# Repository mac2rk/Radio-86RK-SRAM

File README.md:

# Radio-86RK SRAM
The 2012 remake of the 1986 DIY 8-bit computer

## Contents
* [Introduction](#introduction)
* [Specifications](#specifications)
* [Hardware documentation](#hardware-documentation)
  * [Schematic and PCB Layout](#schematic-and-pcb-layout)
  * [Connectors](#connectors)
  * [Bill of Materials](#bill-of-materials)
  * [Memory Map](#memory-map)
* [Firmware documentation](#firmware-documentation)
  * [Monitor](#monitor)
  * [PS/2 adapter](#ps2-adapter)
* [Known Issues](#known-issues)

## Introduction
This project is a 2012 remake of [Radio-86RK](https://en.wikipedia.org/wiki/Radio-86RK), a DIY 8-bit computer the original design for which was published in 1986 by the Soviet *Radio* ham and DIY electronics magazine (hence the "Radio" and "86" in the name).

The original 1986 design targeted an enthusiast building it from scratch and was notable for its relative simplicity. Like most home computers of the era, it uses TV for video output and a cassette tape for program storage. Unlike most home computers, there is no color and no bitmapped graphics. You can get a feel of it via @begoon's excellent online [emulator](https://rk86.ru/) (the emulator's source code is [available on GitHub](https://github.com/begoon/rk86-js)).

The principal motivation behind this project was to replace the obsolete 1-bit DRAM memory and its supporting logic (address multiplexers, etc.) with a single 32KiB static RAM chip. A number of other changes has been made - see the [schematic](Eagle/Radio-86RK-SRAM-Schematic.pdf) for details. The project was initially [published](http://radio86rk.pbworks.com) around 2012 and since then has been built by a number of people, with one build even landing at the [Center for Computing History](http://www.computinghistory.org.uk/det/32376/Radio-86RK-(Russia)/) in Cambridge, thanks to @begoon. Also, this project seems to have inspired other designs, particularly @skiselev's [Radio-86RK](https://github.com/skiselev/radio-86rk) and [Радио-86РК-SRAM-128K](http://www.nedopc.org/forum/viewtopic.php?t=10660&start=0) by @shaos. 

## Specifications
  * CPU: Intel i8080 @ 2MHz
  * Memory: 32KiB RAM, 8 KiB ROM, optional 32KiB ROM cartridge (built-in or external)
  * Display: 64x25 alphanumeric monochrome (50Hz composite video output suitable for TV)
  * Keyboard: Proprietary 66-key (parallel interface) or any standard PS/2 (with built-in adapter)
  * Sound: 1-bit digital
  * I/O: Cassette tape recorder (use [mac2rk](https://github.com/mac2rk/mac2rk) to emulate tape recorder with a sound card)
  * Expansion: optional parallel port (required for ROM cartridges) 
  * Software: 2KiB ROM monitor; additional software can be loaded from a ROM cartridge or tape
  * Form factor: Mini-ITX (170x170 mm, 6.7x6.7 inch)
  * Power supply: 18-36VDC @ approx. 5W via barrel connector

## Hardware documentation

### Schematic and PCB Layout
[Schematic](Eagle/Radio-86RK-SRAM-Schematic.pdf)
[PCB Layout](Eagle/Radio-86RK-SRAM-Silk.pdf)

The computer is built around an Intel i8080 CPU (D6 on the schematic) with i8224 clock generator (D1). RAM and ROM are implemented with 62256 SRAM (D22) and 28C64 EEPROM (D17), respectively. Video subsystem includes an i8275 CRT controller (D8), i8257 DMA controller (D2) with address latch (D7), 28C16 font EEPROM (D12) and a parallel-in, serial-out shift register (D15). Two i8255 Programmable Peripheral Interfaces (PPIs) provide I/O connectivity. One PPI (D20) interfaces a cassete tape recorder and the parallel keyboard; a PS/2 keyboard can be connected via an onboard adapter (D30). The second PPI (D14) implements the expansion port, which can be used, among other things, to connect ROM cartridges. A 28C256 ROM cartridge can be either installed onboard (D30) or connected via a 26-way expansion header. The onboard power supply with power sequencing is built with three DC/DC converter modules (D33..D35) and an opamp (D32).

### Connectors
[Connectors](docs/Connectors.md)

### Bill of Materials
[Bill of Materials](docs/BOM.md)

### Memory Map
[Memory Map](docs/Memory_map.md)

## Firmware Documentation

### Monitor

[Monitor commands and subroutines](docs/Monitor.md)

### PS/2 adapter
The PS/2 to parallel keyboard adapter based on an ATmega48/88/168/328 MCU was developed and [published](https://zx-pk.ru/threads/9294-orion-128-kontroller-ps-2-klaviatury.html) by Kamil Karimov (caro). The source code for the adapter is not available, but the binary is known to work. Note that this adapter requires that the keyboard support Scan Code Set 3. Most do, but some (e.g. Logitech K100) don't and will not work properly with the adapter.

There are two separate versions of the compiled binary: one for ATmega48/88 and one for ATmega168/328. When programming the ATmega, all fuses except CKDIV8 should be left in their default states. CKDIV8 should be left unprogrammed. (CKDIV8 is programmed by default, which clocks the ATmega at 1MHz. With this clock, only Caps Lock (= Rus/Lat) and Print Screen (= Reset) will work normally. Other keys will not work at all or will work partially or intermittently.)

## Known Issues

* Top silkscreen: R109, which sets the current for the "+12V" LED, has a wrong value. Instead oof 330 ohm, it should be between 1kOhm and 1.5kOhm
* PS/2 adapter requires that the keyboard support Scan Code Set 3. Most do, but some (e.g. Logitech K100) don't and do not work properly with the adapter.

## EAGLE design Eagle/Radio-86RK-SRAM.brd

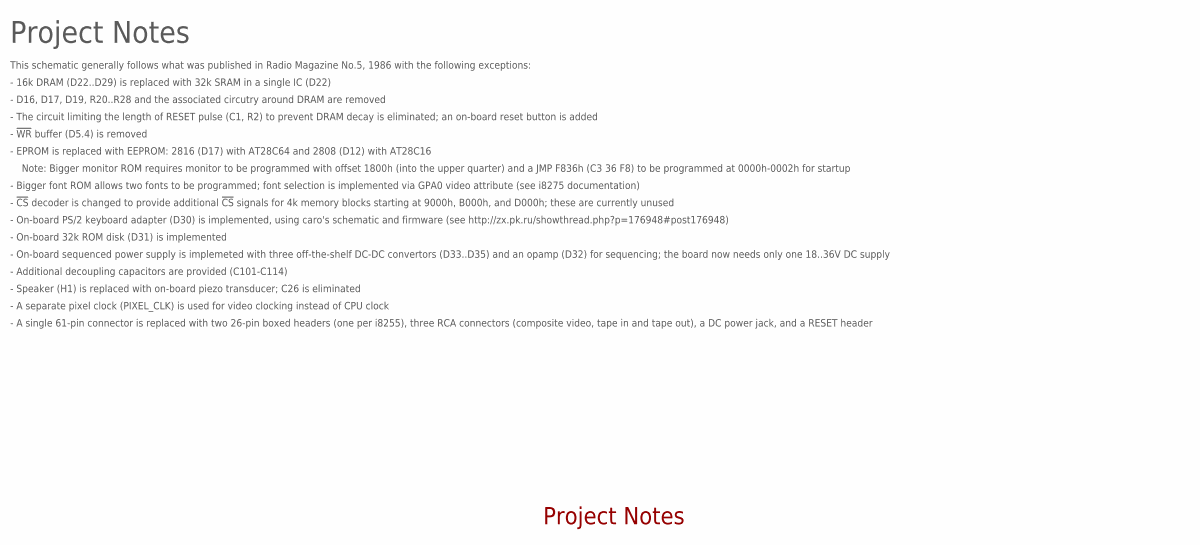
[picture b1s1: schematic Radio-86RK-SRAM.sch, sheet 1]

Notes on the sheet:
Project Notes
This schematic generally follows what was published in Radio Magazine No.5, 1986 with the following exceptions:
- 16k DRAM (D22..D29) is replaced with 32k SRAM in a single IC (D22)
- D16, D17, D19, R20..R28 and the associated circutry around DRAM are removed
- EPROM is replaced with EEPROM: 2816 (D17) with AT28C64 and 2808 (D12) with AT28C16
- !WR! buffer (D5.4) is removed
- !CS! decoder is changed to provide additional !CS! signals for 4k memory blocks starting at 9000h, B000h, and D000h; these are currently unused
Note: Bigger monitor ROM requires monitor to be programmed with offset 1800h (into the upper quarter) and a JMP F836h (C3 36 F8) to be programmed at 0000h-0002h for startup
- Bigger font ROM allows two fonts to be programmed; font selection is implemented via GPA0 video attribute (see i8275 documentation)
- On-board sequenced power supply is implemeted with three off-the-shelf DC-DC convertors (D33..D35) and an opamp (D32) for sequencing; the board now needs only one 18..36V DC supply
- Additional decoupling capacitors are provided (C101-C114)
- On-board PS/2 keyboard adapter (D30) is implemented, using caro's schematic and firmware (see http://zx.pk.ru/showthread.php?p=176948#post176948)
- On-board 32k ROM disk (D31) is implemented
- Speaker (H1) is replaced with on-board piezo transducer; C26 is eliminated
- A separate pixel clock (PIXEL_CLK) is used for video clocking instead of CPU clock
- A single 61-pin connector is replaced with two 26-pin boxed headers (one per i8255), three RCA connectors (composite video, tape in and tape out), a DC power jack, and a RESET header
- The circuit limiting the length of RESET pulse (C1, R2) to prevent DRAM decay is eliminated; an on-board reset button is added

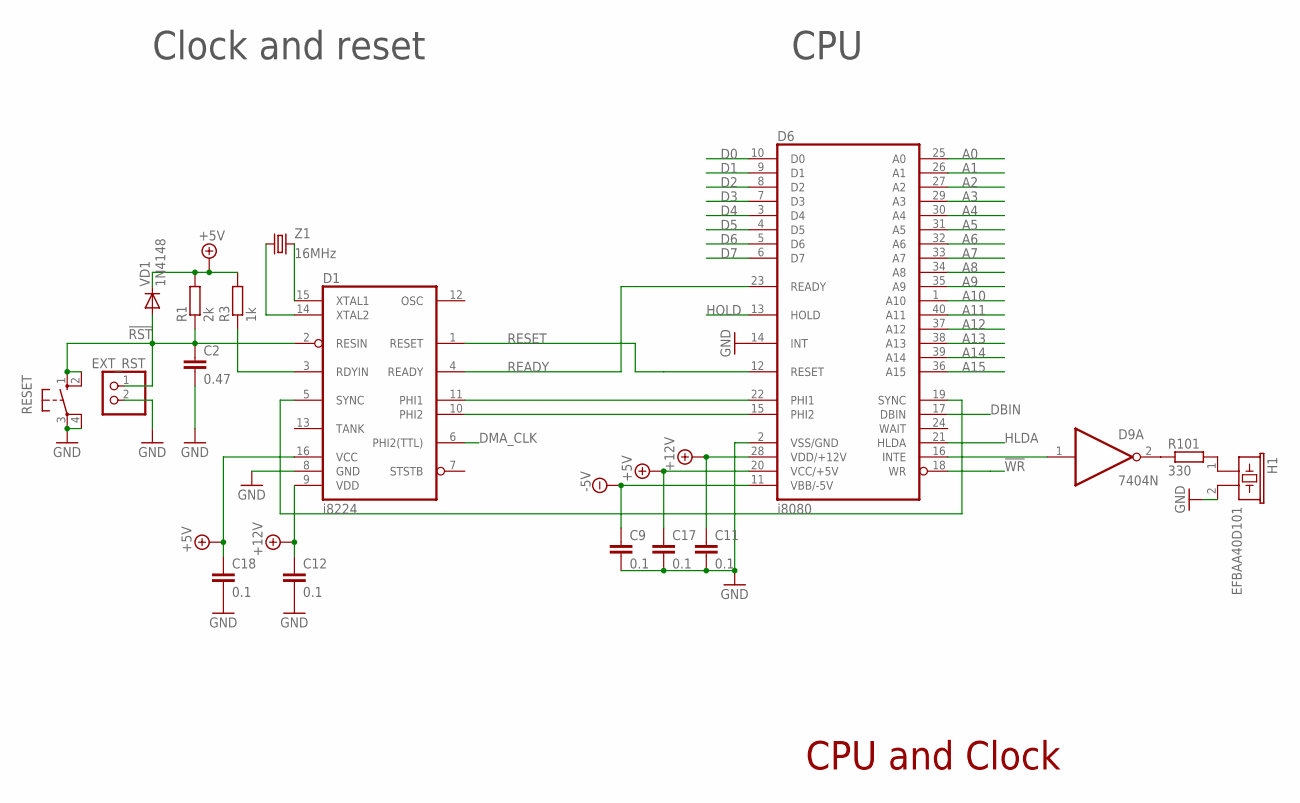
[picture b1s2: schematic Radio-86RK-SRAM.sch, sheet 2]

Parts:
C2: 0.47; C050-024X044
C9, C11, C12, C17, C18: 0.1; C050-024X044
D1: i8224; DIL16
D6: i8080; DIL40
D9: 7404N; DIL14
EXT_RST: PINHD-1X2; 1X02
H1: EFBAA40D101
R1: 2k; 0207/10
R3: 1k; 0207/10
R101: 330; 0207/10
RESET: 10-XX; B3F-10XX
VD1: 1N4148; DO35-10
Z1: 16MHz; HC49U-V

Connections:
!RST: C2.1, D1.2 (RESIN), EXT_RST.1, R1.1, RESET.1 (S), RESET.2 (S1), VD1.A; also elsewhere on the board
!WR: D6.18 (WR); also elsewhere on the board
+5V: C17.1, C18.1, D1.16 (VCC), D6.20 (VCC/+5V), R1.2, R3.2, VD1.C; also elsewhere on the board
+12V: C11.1, C12.1, D1.9 (VDD), D6.28 (VDD/+12V); also elsewhere on the board
-5V: C9.1, D6.11 (VBB/-5V); also elsewhere on the board
A0: D6.25 (A0); also elsewhere on the board
A1: D6.26 (A1); also elsewhere on the board
A2: D6.27 (A2); also elsewhere on the board
A3: D6.29 (A3); also elsewhere on the board
A4: D6.30 (A4); also elsewhere on the board
A5: D6.31 (A5); also elsewhere on the board
A6: D6.32 (A6); also elsewhere on the board
A7: D6.33 (A7); also elsewhere on the board
A8: D6.34 (A8); also elsewhere on the board
A9: D6.35 (A9); also elsewhere on the board
A10: D6.1 (A10); also elsewhere on the board
A11: D6.40 (A11); also elsewhere on the board
A12: D6.37 (A12); also elsewhere on the board
A13: D6.38 (A13); also elsewhere on the board
A14: D6.39 (A14); also elsewhere on the board
A15: D6.36 (A15); also elsewhere on the board
D0: D6.10 (D0); also elsewhere on the board
D1: D6.9 (D1); also elsewhere on the board
D2: D6.8 (D2); also elsewhere on the board
D3: D6.7 (D3); also elsewhere on the board
D4: D6.3 (D4); also elsewhere on the board
D5: D6.4 (D5); also elsewhere on the board
D6: D6.5 (D6); also elsewhere on the board
D7: D6.6 (D7); also elsewhere on the board
DBIN: D6.17 (DBIN); also elsewhere on the board
DMA_CLK: D1.6 (PHI2(TTL)); also elsewhere on the board
GND: C2.2, C9.2, C11.2, C12.2, C17.2, C18.2, D1.8 (GND), D6.2 (VSS/GND), D6.14 (INT), EXT_RST.2, H1.2, RESET.3, RESET.4 (P1); also elsewhere on the board
HLDA: D6.21 (HLDA); also elsewhere on the board
HOLD: D6.13 (HOLD); also elsewhere on the board
unnamed: D1.11 (PHI1), D6.22 (PHI1)
unnamed: D1.10 (PHI2), D6.15 (PHI2)
unnamed: D1.15 (XTAL1), Z1.2
unnamed: D1.14 (XTAL2), Z1.1
unnamed: D1.5 (SYNC), D6.19 (SYNC)
unnamed: D1.3 (RDYIN), R3.1
unnamed: D6.16 (INTE), D9.1 (I)
unnamed: H1.1, R101.2
unnamed: D9.2 (O), R101.1
READY: D1.4 (READY), D6.23 (READY); also elsewhere on the board
RESET: D1.1 (RESET), D6.12 (RESET); also elsewhere on the board

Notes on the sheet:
CPU and Clock
Clock and reset
CPU

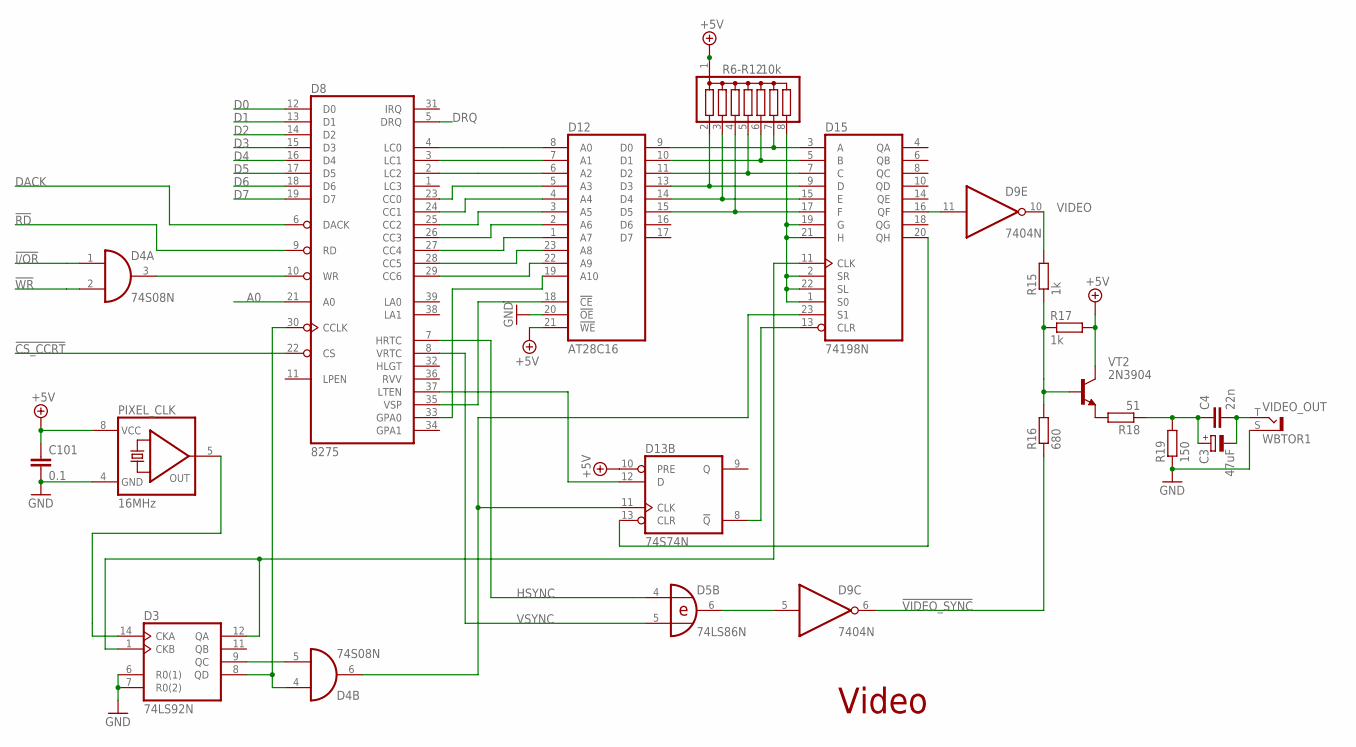
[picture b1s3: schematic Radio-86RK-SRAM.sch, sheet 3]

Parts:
C3: 47uF; E2,5-5
C4: 22n; C050-024X044
C101: 0.1; C050-024X044
D3: 74LS92N; DIL14
D4: 74S08N; DIL14
D5: 74LS86N; DIL14
D8: 8275; DIL40
D9: 7404N; DIL14
D12: AT28C16; DIL24
D13: 74S74N; DIL14
D15: 74198N; DIL24-6
PIXEL_CLK: 16MHz; DIL08S
R6-R12: 10k; SIL8
R15, R17: 1k; 0207/10
R16: 680; 0207/10
R18: 51; 0207/10
R19: 150; 0207/10
VIDEO_OUT: WBTOR1; MPN WBTOR 1 BLACK
VT2: 2N3904; TO92

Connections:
!CS_CCRT: D8.22 (CS); also elsewhere on the board
!I/OR: D4.1 (I0); also elsewhere on the board
!RD: D8.9 (RD); also elsewhere on the board
!VIDEO: D9.11 (I), D15.16 (QF)
!VIDEO_SYNC: D9.6 (O), R16.1
!WR: D4.2 (I1); also elsewhere on the board
+5V: C101.1, D12.21 (!WE), D13.10 (PRE), PIXEL_CLK.8 (VCC), R6-R12.1, R17.2, VT2.1 (C); also elsewhere on the board
A0: D8.21 (A0); also elsewhere on the board
COMPOSITE_VIDEO: C3.-, C4.2, VIDEO_OUT.T
D0: D8.12 (D0); also elsewhere on the board
D1: D8.13 (D1); also elsewhere on the board
D2: D8.14 (D2); also elsewhere on the board
D3: D8.15 (D3); also elsewhere on the board
D4: D8.16 (D4); also elsewhere on the board
D5: D8.17 (D5); also elsewhere on the board
D6: D8.18 (D6); also elsewhere on the board
D7: D8.19 (D7); also elsewhere on the board
DACK: D8.6 (DACK); also elsewhere on the board
DRQ: D8.5 (DRQ); also elsewhere on the board
GND: C101.2, D3.6 (R0(1)), D3.7 (R0(2)), D12.20 (!OE), PIXEL_CLK.4 (GND), R19.1, VIDEO_OUT.S; also elsewhere on the board
HSYNC: D5.4 (I0), D8.7 (HRTC)
unnamed: D3.14 (CKA), PIXEL_CLK.5 (OUT)
unnamed: D3.1 (CKB), D3.12 (QA), D15.11 (CLK)
unnamed: D4.3 (O), D8.10 (WR)
unnamed: D3.9 (QC), D4.5 (I1)
unnamed: D3.8 (QD), D4.4 (I0), D8.30 (CCLK)
unnamed: D8.23 (CC0), D12.5 (A3)
unnamed: D8.24 (CC1), D12.4 (A4)
unnamed: D8.25 (CC2), D12.3 (A5)
unnamed: D8.26 (CC3), D12.2 (A6)
unnamed: D8.27 (CC4), D12.1 (A7)
unnamed: D8.4 (LC0), D12.8 (A0)
unnamed: D8.3 (LC1), D12.7 (A1)
unnamed: D8.2 (LC2), D12.6 (A2)
unnamed: D8.35 (VSP), D12.18 (!CE)
unnamed: D12.9 (D0), D15.3 (A), R6-R12.7
unnamed: D8.28 (CC5), D12.23 (A8)
unnamed: D8.29 (CC6), D12.22 (A9)
unnamed: D12.10 (D1), D15.5 (B), R6-R12.6
unnamed: D12.11 (D2), D15.7 (C), R6-R12.5
unnamed: D12.13 (D3), D15.9 (D), R6-R12.2
unnamed: D12.14 (D4), D15.15 (E), R6-R12.3
unnamed: D12.15 (D5), D15.17 (F), R6-R12.4
unnamed: D13.13 (CLR), D15.20 (QH)
unnamed: D13.8 (!Q), D15.13 (CLR)
unnamed: D4.6 (O), D13.11 (CLK), D15.23 (S1)
unnamed: D8.37 (LTEN), D13.12 (D)
unnamed: R15.1, R16.2, R17.1, VT2.2 (B)
unnamed: D5.6 (O), D9.5 (I)
unnamed: R18.2, VT2.3 (E)
unnamed: C3.+, C4.1, R18.1, R19.2
unnamed: D8.33 (GPA0), D12.19 (A10)
unnamed: D15.1 (S0), D15.2 (SR), D15.19 (G), D15.21 (H), D15.22 (SL), R6-R12.8
VIDEO: D9.10 (O), R15.2
VSYNC: D5.5 (I1), D8.8 (VRTC)

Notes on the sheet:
Video

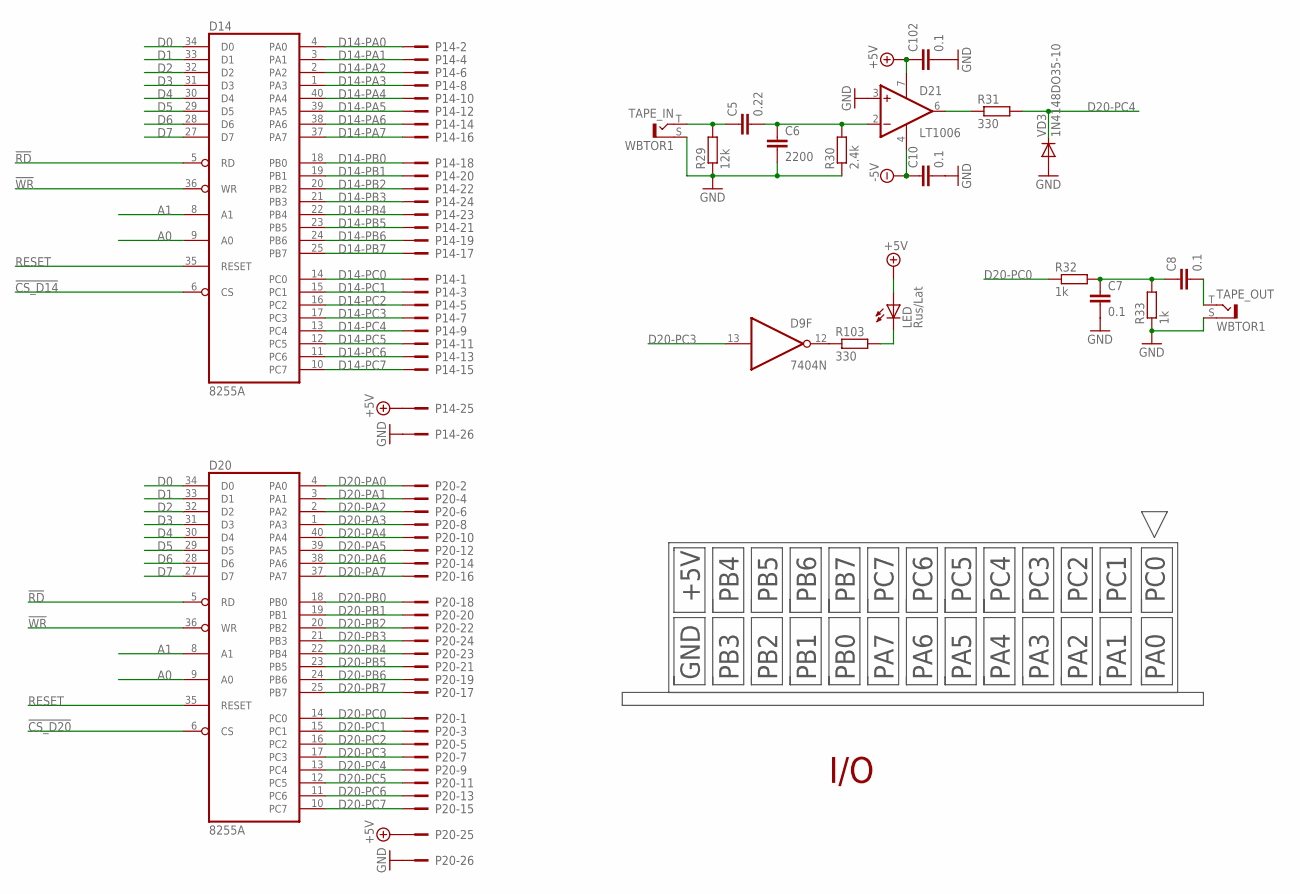
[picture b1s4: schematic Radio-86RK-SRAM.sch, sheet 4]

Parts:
C5: 0.22; C050-024X044
C6: 2200; C050-024X044
C7, C8, C10, C102: 0.1; C050-024X044
D9: 7404N; DIL14
D14, D20: 8255A; DIL40
D21: LT1006; DIL08
LED: Rus/Lat; LED3MM
P14, P20: 2526-5; PAK100/2500-5-26
R29: 12k; 0207/10
R30: 2.4k; 0207/10
R31, R103: 330; 0207/10
R32, R33: 1k; 0207/10
TAPE_IN: WBTOR1; MPN WBTOR 1 BLACK
TAPE_OUT: WBTOR1; MPN WBTOR 1 BLACK
VD3: 1N4148DO35-10; DO35-10

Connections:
!CS_D14: D14.6 (CS); also elsewhere on the board
!CS_D20: D20.6 (CS); also elsewhere on the board
!RD: D14.5 (RD), D20.5 (RD); also elsewhere on the board
!WR: D14.36 (WR), D20.36 (WR); also elsewhere on the board
+5V: C102.1, D21.7 (V+), LED.A, P14.25, P20.25; also elsewhere on the board
-5V: C10.1, D21.4 (V-); also elsewhere on the board
A0: D14.9 (A0), D20.9 (A0); also elsewhere on the board
A1: D14.8 (A1), D20.8 (A1); also elsewhere on the board
D0: D14.34 (D0), D20.34 (D0); also elsewhere on the board
D1: D14.33 (D1), D20.33 (D1); also elsewhere on the board
D2: D14.32 (D2), D20.32 (D2); also elsewhere on the board
D3: D14.31 (D3), D20.31 (D3); also elsewhere on the board
D4: D14.30 (D4), D20.30 (D4); also elsewhere on the board
D5: D14.29 (D5), D20.29 (D5); also elsewhere on the board
D6: D14.28 (D6), D20.28 (D6); also elsewhere on the board
D7: D14.27 (D7), D20.27 (D7); also elsewhere on the board
D14-PA0: D14.4 (PA0), P14.2; also elsewhere on the board
D14-PA1: D14.3 (PA1), P14.4; also elsewhere on the board
D14-PA2: D14.2 (PA2), P14.6; also elsewhere on the board
D14-PA3: D14.1 (PA3), P14.8; also elsewhere on the board
D14-PA4: D14.40 (PA4), P14.10; also elsewhere on the board
D14-PA5: D14.39 (PA5), P14.12; also elsewhere on the board
D14-PA6: D14.38 (PA6), P14.14; also elsewhere on the board
D14-PA7: D14.37 (PA7), P14.16; also elsewhere on the board
D14-PB0: D14.18 (PB0), P14.18; also elsewhere on the board
D14-PB1: D14.19 (PB1), P14.20; also elsewhere on the board
D14-PB2: D14.20 (PB2), P14.22; also elsewhere on the board
D14-PB3: D14.21 (PB3), P14.24; also elsewhere on the board
D14-PB4: D14.22 (PB4), P14.23; also elsewhere on the board
D14-PB5: D14.23 (PB5), P14.21; also elsewhere on the board
D14-PB6: D14.24 (PB6), P14.19; also elsewhere on the board
D14-PB7: D14.25 (PB7), P14.17; also elsewhere on the board
D14-PC0: D14.14 (PC0), P14.1; also elsewhere on the board
D14-PC1: D14.15 (PC1), P14.3; also elsewhere on the board
D14-PC2: D14.16 (PC2), P14.5; also elsewhere on the board
D14-PC3: D14.17 (PC3), P14.7; also elsewhere on the board
D14-PC4: D14.13 (PC4), P14.9; also elsewhere on the board
D14-PC5: D14.12 (PC5), P14.11; also elsewhere on the board
D14-PC6: D14.11 (PC6), P14.13; also elsewhere on the board
D14-PC7: D14.10 (PC7), P14.15; also elsewhere on the board
D20-PA0: D20.4 (PA0), P20.2; also elsewhere on the board
D20-PA1: D20.3 (PA1), P20.4; also elsewhere on the board
D20-PA2: D20.2 (PA2), P20.6; also elsewhere on the board
D20-PA3: D20.1 (PA3), P20.8; also elsewhere on the board
D20-PA4: D20.40 (PA4), P20.10; also elsewhere on the board
D20-PA5: D20.39 (PA5), P20.12; also elsewhere on the board
D20-PA6: D20.38 (PA6), P20.14; also elsewhere on the board
D20-PA7: D20.37 (PA7), P20.16; also elsewhere on the board
D20-PB0: D20.18 (PB0), P20.18; also elsewhere on the board
D20-PB1: D20.19 (PB1), P20.20; also elsewhere on the board
D20-PB2: D20.20 (PB2), P20.22; also elsewhere on the board
D20-PB3: D20.21 (PB3), P20.24; also elsewhere on the board
D20-PB4: D20.22 (PB4), P20.23; also elsewhere on the board
D20-PB5: D20.23 (PB5), P20.21; also elsewhere on the board
D20-PB6: D20.24 (PB6), P20.19; also elsewhere on the board
D20-PB7: D20.25 (PB7), P20.17; also elsewhere on the board
D20-PC0: D20.14 (PC0), P20.1, R32.1
D20-PC1: D20.15 (PC1), P20.3
D20-PC2: D20.16 (PC2), P20.5
D20-PC3: D9.13 (I), D20.17 (PC3), P20.7
D20-PC4: D20.13 (PC4), P20.9, R31.2, VD3.C
D20-PC5: D20.12 (PC5), P20.11; also elsewhere on the board
D20-PC6: D20.11 (PC6), P20.13; also elsewhere on the board
D20-PC7: D20.10 (PC7), P20.15; also elsewhere on the board
GND: C6.2, C7.2, C10.2, C102.2, D21.3 (+IN), P14.26, P20.26, R29.1, R30.1, R33.1, TAPE_IN.S, TAPE_OUT.S, VD3.A; also elsewhere on the board
unnamed: D9.12 (O), R103.1
unnamed: LED.K (C), R103.2
unnamed: C5.2, C6.1, D21.2 (-IN), R30.2
unnamed: C7.1, C8.1, R32.2, R33.2
unnamed: D21.6 (OUT), R31.1
unnamed: C5.1, R29.2, TAPE_IN.T
unnamed: C8.2, TAPE_OUT.T
RESET: D14.35 (RESET), D20.35 (RESET); also elsewhere on the board

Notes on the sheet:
I/O
GND
PB3
PB2
PB1
PB0
PA7
PA6
PA5
PA4
PA3
PA2
PA1
PA0
+5V
PB4
PB5
PB6
PB7
PC7
PC6
PC5
PC4
PC3
PC2
PC1
PC0

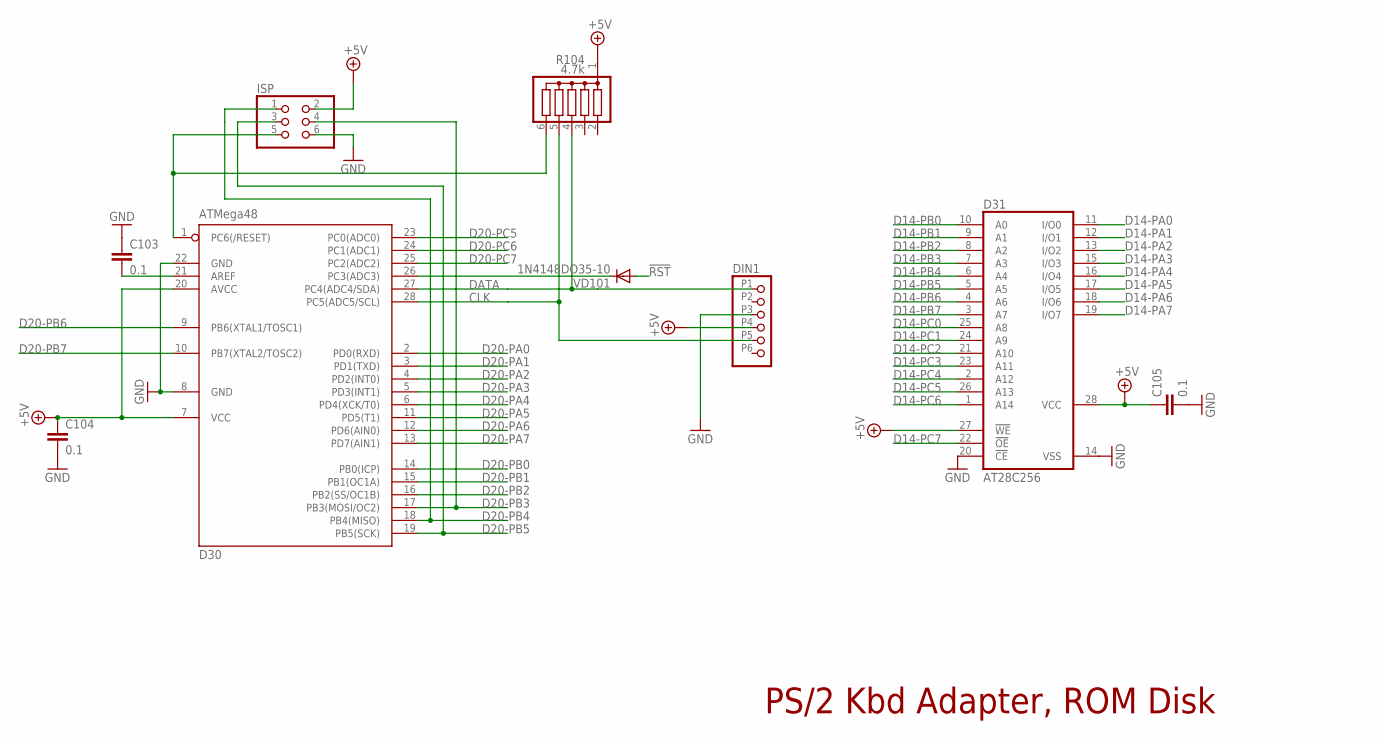
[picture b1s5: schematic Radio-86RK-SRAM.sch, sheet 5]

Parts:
C103, C104, C105: 0.1; C050-024X044
D30: ATMega48; DIL28-3
D31: AT28C256; DIL28-6
DIN1: TM0508A/6; MINI-DIN6
ISP: PINHD-2X3; 2X03
R104: 4.7k; SIL6
VD101: 1N4148DO35-10; DO35-10

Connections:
!RST: VD101.A; also elsewhere on the board
+5V: C104.1, C105.1, D30.7 (VCC), D30.20 (AVCC), D31.27 (!WE), D31.28 (VCC), DIN1.P4 (4), ISP.2, R104.1; also elsewhere on the board
CLK: D30.28 (PC5(ADC5/SCL)), DIN1.P5 (5), R104.5
D14-PA0: D31.11 (I/O0); also elsewhere on the board
D14-PA1: D31.12 (I/O1); also elsewhere on the board
D14-PA2: D31.13 (I/O2); also elsewhere on the board
D14-PA3: D31.15 (I/O3); also elsewhere on the board
D14-PA4: D31.16 (I/O4); also elsewhere on the board
D14-PA5: D31.17 (I/O5); also elsewhere on the board
D14-PA6: D31.18 (I/O6); also elsewhere on the board
D14-PA7: D31.19 (I/O7); also elsewhere on the board
D14-PB0: D31.10 (A0); also elsewhere on the board
D14-PB1: D31.9 (A1); also elsewhere on the board
D14-PB2: D31.8 (A2); also elsewhere on the board
D14-PB3: D31.7 (A3); also elsewhere on the board
D14-PB4: D31.6 (A4); also elsewhere on the board
D14-PB5: D31.5 (A5); also elsewhere on the board
D14-PB6: D31.4 (A6); also elsewhere on the board
D14-PB7: D31.3 (A7); also elsewhere on the board
D14-PC0: D31.25 (A8); also elsewhere on the board
D14-PC1: D31.24 (A9); also elsewhere on the board
D14-PC2: D31.21 (A10); also elsewhere on the board
D14-PC3: D31.23 (A11); also elsewhere on the board
D14-PC4: D31.2 (A12); also elsewhere on the board
D14-PC5: D31.26 (A13); also elsewhere on the board
D14-PC6: D31.1 (A14); also elsewhere on the board
D14-PC7: D31.22 (!OE); also elsewhere on the board
D20-PA0: D30.2 (PD0(RXD)); also elsewhere on the board
D20-PA1: D30.3 (PD1(TXD)); also elsewhere on the board
D20-PA2: D30.4 (PD2(INT0)); also elsewhere on the board
D20-PA3: D30.5 (PD3(INT1)); also elsewhere on the board
D20-PA4: D30.6 (PD4(XCK/T0)); also elsewhere on the board
D20-PA5: D30.11 (PD5(T1)); also elsewhere on the board
D20-PA6: D30.12 (PD6(AIN0)); also elsewhere on the board
D20-PA7: D30.13 (PD7(AIN1)); also elsewhere on the board
D20-PB0: D30.14 (PB0(ICP)); also elsewhere on the board
D20-PB1: D30.15 (PB1(OC1A)); also elsewhere on the board
D20-PB2: D30.16 (PB2(SS/OC1B)); also elsewhere on the board
D20-PB3: D30.17 (PB3(MOSI/OC2)), ISP.4; also elsewhere on the board
D20-PB4: D30.18 (PB4(MISO)), ISP.1; also elsewhere on the board
D20-PB5: D30.19 (PB5(SCK)), ISP.3; also elsewhere on the board
D20-PB6: D30.9 (PB6(XTAL1/TOSC1)); also elsewhere on the board
D20-PB7: D30.10 (PB7(XTAL2/TOSC2)); also elsewhere on the board
D20-PC5: D30.23 (PC0(ADC0)); also elsewhere on the board
D20-PC6: D30.24 (PC1(ADC1)); also elsewhere on the board
D20-PC7: D30.25 (PC2(ADC2)); also elsewhere on the board
DATA: D30.27 (PC4(ADC4/SDA)), DIN1.P1 (1), R104.4
GND: C103.1, C104.2, C105.2, D30.8 (GND), D30.22 (GND), D31.14 (VSS), D31.20 (!CE), DIN1.G1 (GND), DIN1.G2 (GND), DIN1.G3 (GND), DIN1.P3 (3), ISP.6; also elsewhere on the board
unnamed: C103.2, D30.21 (AREF)
unnamed: D30.1 (PC6(/RESET)), ISP.5, R104.6
unnamed: D30.26 (PC3(ADC3)), VD101.C

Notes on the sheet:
PS/2 Kbd Adapter, ROM Disk

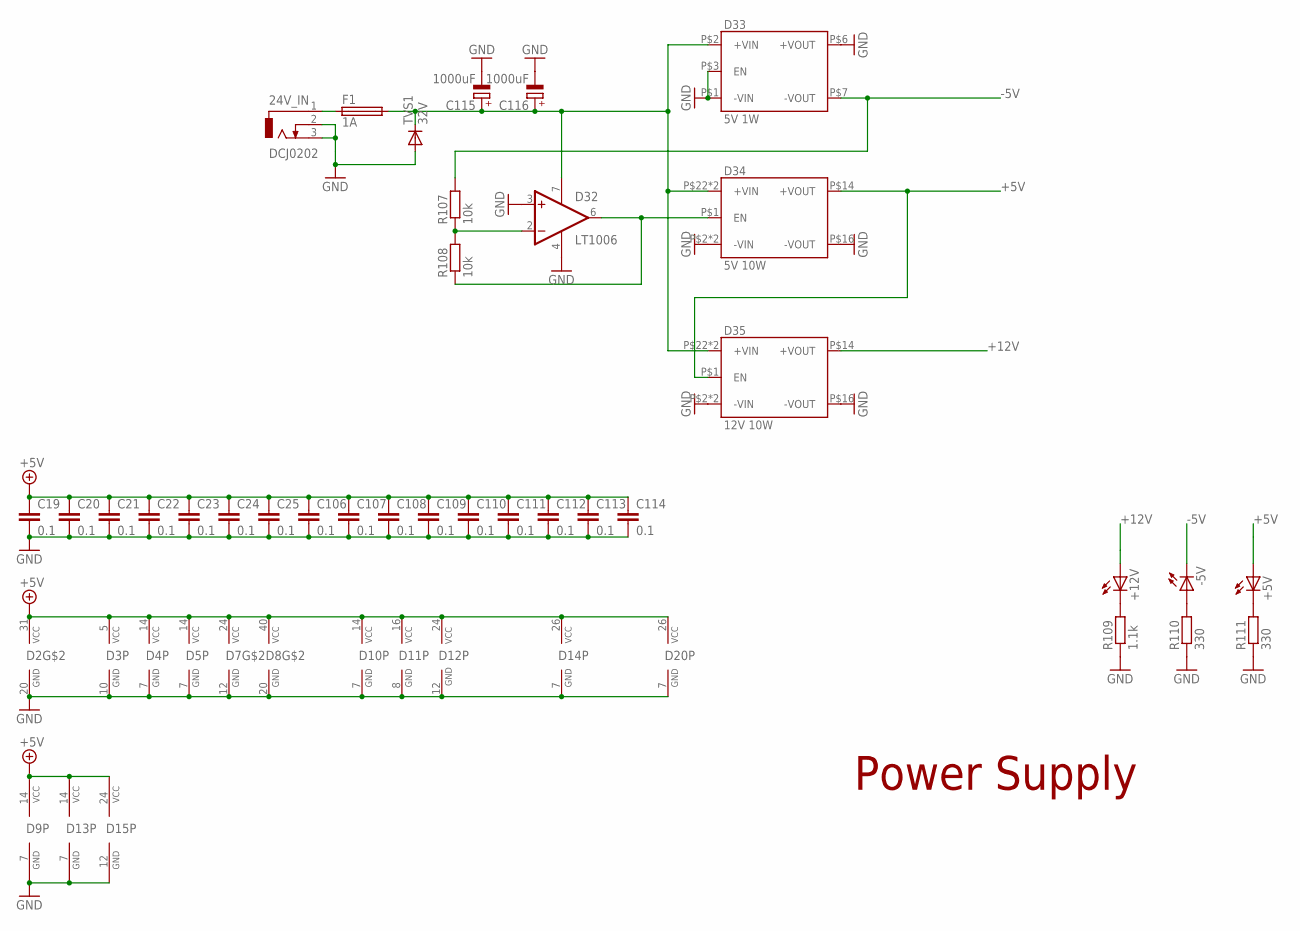
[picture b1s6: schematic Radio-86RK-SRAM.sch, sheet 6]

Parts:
24V_IN: DCJ0202
+5V, +12V: LED3MM
-5V: LED3MM
C19, C20, C21, C22, C23, C24, C25, C106, C107, C108, C109, C110, C111, C112, C113, C114: 0.1; C050-024X044
C115: 1000uF; E5-13
C116: 1000uF; E7,5-18
D2: i8257; DIL40
D3: 74LS92N; DIL14
D4: 74S08N; DIL14
D5: 74LS86N; DIL14
D7: 8212; DIL24-6
D8: 8275; DIL40
D9: 7404N; DIL14
D10: 74LS00N; DIL14
D11: 74LS138N; DIL16
D12: AT28C16; DIL24
D13: 74S74N; DIL14
D14, D20: 8255A; DIL40
D15: 74198N; DIL24-6
D32: LT1006; DIL08
D33: 5V 1W; DC/DC_SIP
D34: 5V 10W; DC/DC_24PIN
D35: 12V 10W; DC/DC_24PIN
F1: 1A; TE5
R107, R108: 10k; 0207/10
R109: 1.1k; 0207/10
R110, R111: 330; 0207/10
TVS1: 32V; DO41-10

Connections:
+5V: +5V.A, C19.1, C20.1, C21.1, C22.1, C23.1, C24.1, C25.1, C106.1, C107.1, C108.1, C109.1, C110.1, C111.1, C112.1, C113.1, C114.1, D2.31 (VCC), D3.5 (VCC), D4.14 (VCC), D5.14 (VCC), D7.24 (VCC), D8.40 (VCC), D9.14 (VCC), D10.14 (VCC), D11.16 (VCC), D12.24 (VCC), D13.14 (VCC), D14.26 (VCC), D15.24 (VCC), D20.26 (VCC), D34.P$14 (+VOUT), D35.P$1 (EN); also elsewhere on the board
+12V: +12V.A, D35.P$14 (+VOUT); also elsewhere on the board
-5V: -5V.K (C), D33.P$7 (-VOUT), R107.2; also elsewhere on the board
GND: 24V_IN.2, 24V_IN.3, C19.2, C20.2, C21.2, C22.2, C23.2, C24.2, C25.2, C106.2, C107.2, C108.2, C109.2, C110.2, C111.2, C112.2, C113.2, C114.2, C115.-, C116.-, D2.20 (GND), D3.10 (GND), D4.7 (GND), D5.7 (GND), D7.12 (GND), D8.20 (GND), D9.7 (GND), D10.7 (GND), D11.8 (GND), D12.12 (GND), D13.7 (GND), D14.7 (GND), D15.12 (GND), D20.7 (GND), D32.3 (+IN), D32.4 (V-), D33.P$1 (-VIN), D33.P$3 (EN), D33.P$6 (+VOUT), D34.P$2 (-VIN), D34.P$3 (-VIN), D34.P$16 (-VOUT), D35.P$2 (-VIN), D35.P$3 (-VIN), D35.P$16 (-VOUT), R109.1, R110.1, R111.1, TVS1.A; also elsewhere on the board
unnamed: +5V.K (C), R111.2
unnamed: +12V.K (C), R109.2
unnamed: -5V.A, R110.2
unnamed: 24V_IN.1, F1.1
unnamed: C115.+, C116.+, D32.7 (V+), D33.P$2 (+VIN), D34.P$22 (+VIN), D34.P$23 (+VIN), D35.P$22 (+VIN), D35.P$23 (+VIN), F1.2, TVS1.C
unnamed: D32.6 (OUT), D34.P$1 (EN), R108.1
unnamed: D32.2 (-IN), R107.1, R108.2

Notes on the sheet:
Power Supply

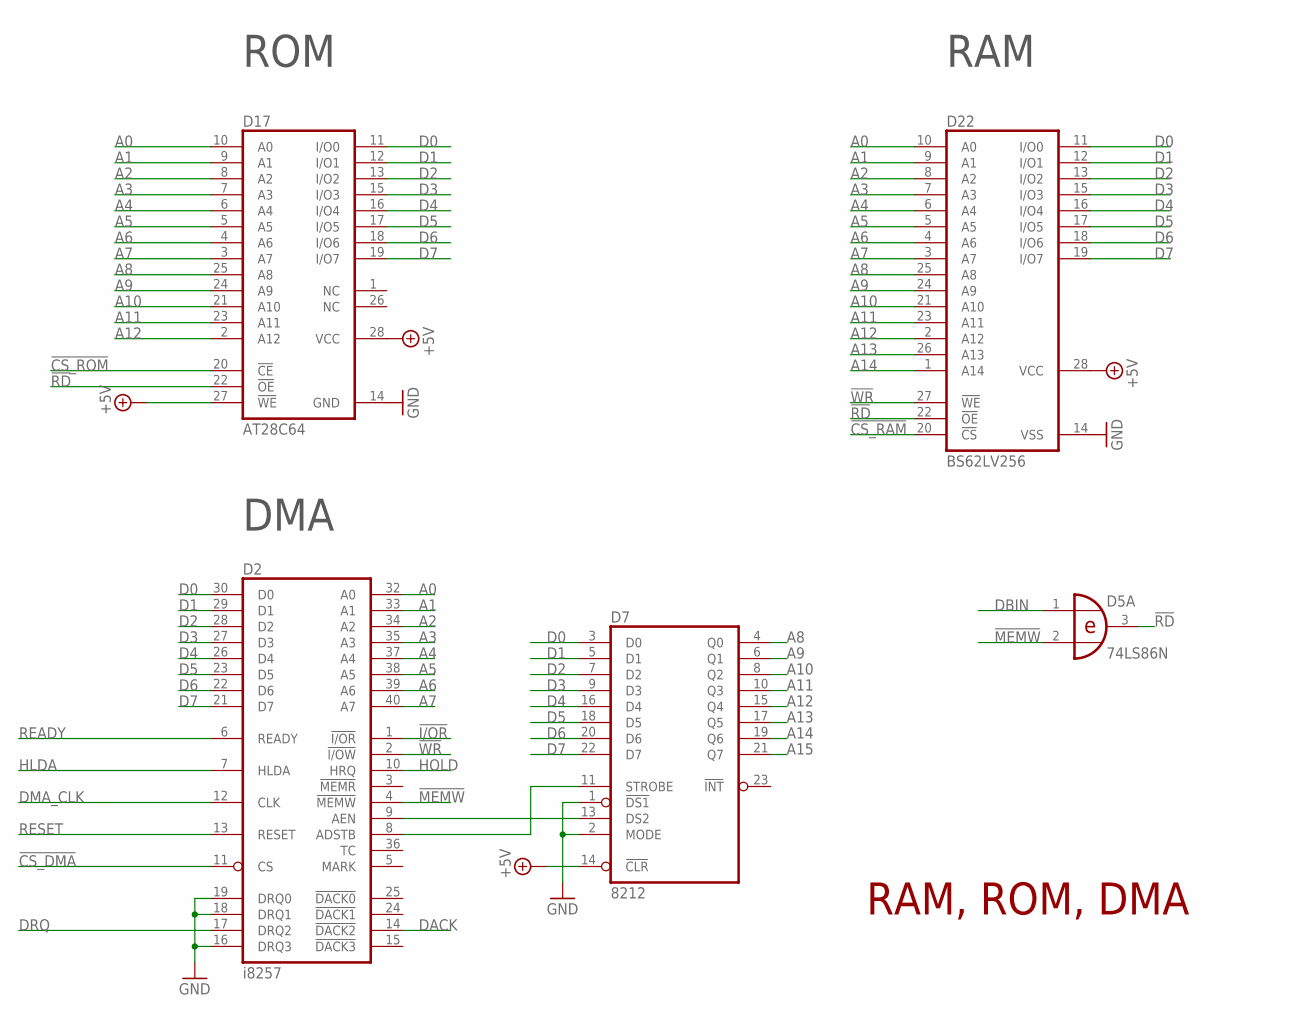
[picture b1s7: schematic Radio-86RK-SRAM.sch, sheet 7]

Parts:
D2: i8257; DIL40
D5: 74LS86N; DIL14
D7: 8212; DIL24-6
D17: AT28C64; DIL28-6
D22: BS62LV256; DIL28-6

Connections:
!CS_DMA: D2.11 (CS); also elsewhere on the board
!CS_RAM: D22.20 (!CS); also elsewhere on the board
!CS_ROM: D17.20 (!CE); also elsewhere on the board
!I/OR: D2.1 (!I/OR); also elsewhere on the board
!MEMW: D2.4 (!MEMW), D5.2 (I1); also elsewhere on the board
!RD: D5.3 (O), D17.22 (!OE), D22.22 (!OE); also elsewhere on the board
!WR: D2.2 (!I/OW), D22.27 (!WE); also elsewhere on the board
+5V: D7.14 (!CLR), D17.27 (!WE), D17.28 (VCC), D22.28 (VCC); also elsewhere on the board
A0: D2.32 (A0), D17.10 (A0), D22.10 (A0); also elsewhere on the board
A1: D2.33 (A1), D17.9 (A1), D22.9 (A1); also elsewhere on the board
A2: D2.34 (A2), D17.8 (A2), D22.8 (A2); also elsewhere on the board
A3: D2.35 (A3), D17.7 (A3), D22.7 (A3); also elsewhere on the board
A4: D2.37 (A4), D17.6 (A4), D22.6 (A4); also elsewhere on the board
A5: D2.38 (A5), D17.5 (A5), D22.5 (A5); also elsewhere on the board
A6: D2.39 (A6), D17.4 (A6), D22.4 (A6); also elsewhere on the board
A7: D2.40 (A7), D17.3 (A7), D22.3 (A7); also elsewhere on the board
A8: D7.4 (Q0), D17.25 (A8), D22.25 (A8); also elsewhere on the board
A9: D7.6 (Q1), D17.24 (A9), D22.24 (A9); also elsewhere on the board
A10: D7.8 (Q2), D17.21 (A10), D22.21 (A10); also elsewhere on the board
A11: D7.10 (Q3), D17.23 (A11), D22.23 (A11); also elsewhere on the board
A12: D7.15 (Q4), D17.2 (A12), D22.2 (A12); also elsewhere on the board
A13: D7.17 (Q5), D22.26 (A13); also elsewhere on the board
A14: D7.19 (Q6), D22.1 (A14); also elsewhere on the board
A15: D7.21 (Q7); also elsewhere on the board
D0: D2.30 (D0), D7.3 (D0), D17.11 (I/O0), D22.11 (I/O0); also elsewhere on the board
D1: D2.29 (D1), D7.5 (D1), D17.12 (I/O1), D22.12 (I/O1); also elsewhere on the board
D2: D2.28 (D2), D7.7 (D2), D17.13 (I/O2), D22.13 (I/O2); also elsewhere on the board
D3: D2.27 (D3), D7.9 (D3), D17.15 (I/O3), D22.15 (I/O3); also elsewhere on the board
D4: D2.26 (D4), D7.16 (D4), D17.16 (I/O4), D22.16 (I/O4); also elsewhere on the board
D5: D2.23 (D5), D7.18 (D5), D17.17 (I/O5), D22.17 (I/O5); also elsewhere on the board
D6: D2.22 (D6), D7.20 (D6), D17.18 (I/O6), D22.18 (I/O6); also elsewhere on the board
D7: D2.21 (D7), D7.22 (D7), D17.19 (I/O7), D22.19 (I/O7); also elsewhere on the board
DACK: D2.14 (!DACK2); also elsewhere on the board
DBIN: D5.1 (I0); also elsewhere on the board
DMA_CLK: D2.12 (CLK); also elsewhere on the board
DRQ: D2.17 (DRQ2); also elsewhere on the board
GND: D2.16 (DRQ3), D2.18 (DRQ1), D2.19 (DRQ0), D7.1 (!DS1), D7.2 (MODE), D17.14 (GND), D22.14 (VSS); also elsewhere on the board
HLDA: D2.7 (HLDA); also elsewhere on the board
HOLD: D2.10 (HRQ); also elsewhere on the board
unnamed: D2.8 (ADSTB), D7.11 (STROBE)
unnamed: D2.9 (AEN), D7.13 (DS2)
READY: D2.6 (READY); also elsewhere on the board
RESET: D2.13 (RESET); also elsewhere on the board

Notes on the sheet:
RAM, ROM, DMA
ROM
RAM
DMA

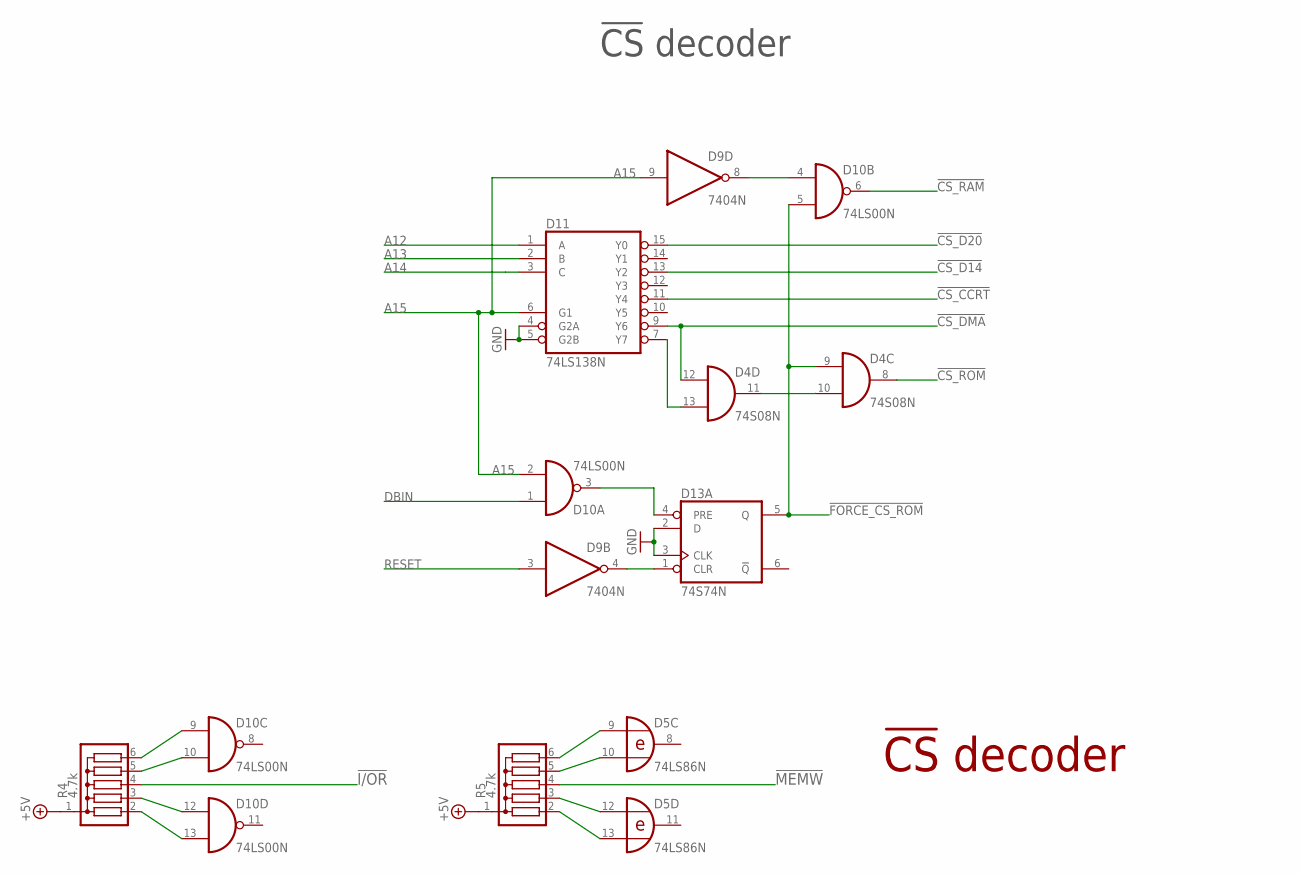
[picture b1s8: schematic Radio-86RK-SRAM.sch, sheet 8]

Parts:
D4: 74S08N; DIL14
D5: 74LS86N; DIL14
D9: 7404N; DIL14
D10: 74LS00N; DIL14
D11: 74LS138N; DIL16
D13: 74S74N; DIL14
R4, R5: 4.7k; SIL6

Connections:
!CS_CCRT: D11.11 (Y4); also elsewhere on the board
!CS_D14: D11.13 (Y2); also elsewhere on the board
!CS_D20: D11.15 (Y0); also elsewhere on the board
!CS_DMA: D4.12 (I0), D11.9 (Y6); also elsewhere on the board
!CS_F000: D4.13 (I1), D11.7 (Y7)
!CS_RAM: D10.6 (O); also elsewhere on the board
!CS_ROM: D4.8 (O); also elsewhere on the board
!FORCE_CS_ROM: D4.9 (I0), D10.5 (I1), D13.5 (Q)
!I/OR: R4.4; also elsewhere on the board
!MEMW: R5.4; also elsewhere on the board
+5V: R4.1, R5.1; also elsewhere on the board
A12: D11.1 (A); also elsewhere on the board
A13: D11.2 (B); also elsewhere on the board
A14: D11.3 (C); also elsewhere on the board
A15: D9.9 (I), D10.2 (I1), D11.6 (G1); also elsewhere on the board
DBIN: D10.1 (I0); also elsewhere on the board
GND: D11.4 (G2A), D11.5 (G2B), D13.2 (D), D13.3 (CLK); also elsewhere on the board
unnamed: D10.3 (O), D13.4 (PRE)
unnamed: D9.4 (O), D13.1 (CLR)
unnamed: D4.10 (I1), D4.11 (O)
unnamed: D9.8 (O), D10.4 (I0)
unnamed: D10.13 (I1), R4.2
unnamed: D10.12 (I0), R4.3
unnamed: D10.10 (I1), R4.5
unnamed: D10.9 (I0), R4.6
unnamed: D5.13 (I1), R5.2
unnamed: D5.12 (I0), R5.3
unnamed: D5.10 (I1), R5.5
unnamed: D5.9 (I0), R5.6
RESET: D9.3 (I); also elsewhere on the board

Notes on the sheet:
!CS! decoder
